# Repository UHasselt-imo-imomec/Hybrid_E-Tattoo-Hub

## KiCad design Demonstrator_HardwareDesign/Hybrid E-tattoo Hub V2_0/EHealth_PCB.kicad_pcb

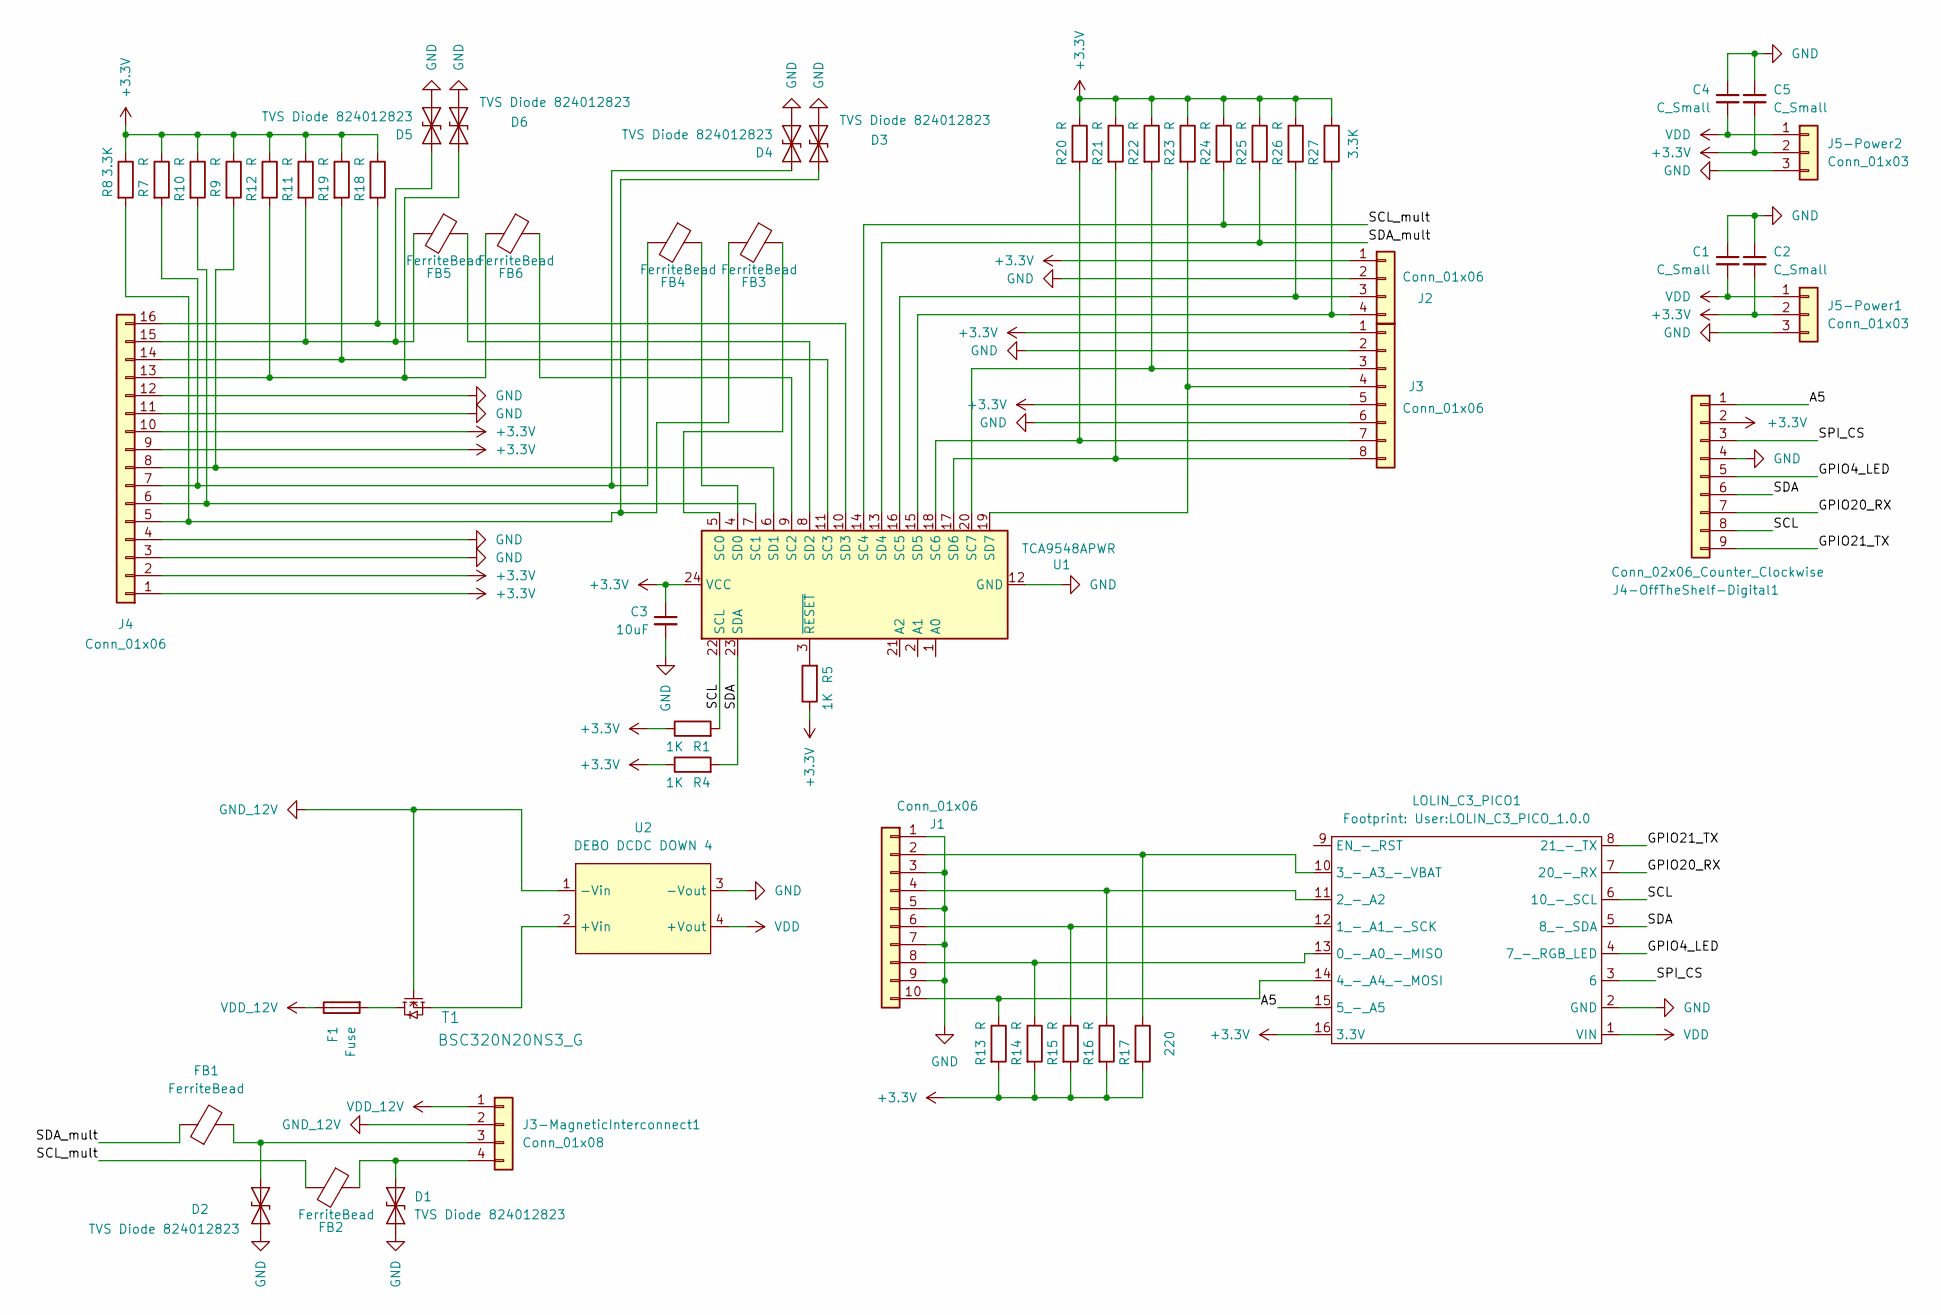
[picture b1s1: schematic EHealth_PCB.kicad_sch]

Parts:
C1, C2, C4, C5: C_Small; C_0805_2012Metric_Pad1.18x1.45mm_HandSolder
C3: 10uF; C_0805_2012Metric_Pad1.18x1.45mm_HandSolder
D1, D2, D3, D4, D5, D6: TVS Diode 824012823; R_0603_1608Metric_Pad0.98x0.95mm_HandSolder
F1: Fuse; Fuse_0805_2012Metric_Pad1.15x1.40mm_HandSolder
FB1, FB2, FB3, FB4, FB5, FB6: FerriteBead; R_0805_2012Metric_Pad1.20x1.40mm_HandSolder
J1: Conn_01x06; PinHeader_2x05_P2.54mm_Vertical
J2: Conn_01x06; PinHeader_1x04_P2.54mm_Vertical
J3: Conn_01x06; PinHeader_1x08_P2.54mm_Vertical
J3-MagneticInterconnect1: Conn_01x08; JST_VH_B4P-VH-B_1x04_P3.96mm_Vertical
J4: Conn_01x06; PinHeader_2x08_P2.54mm_Vertical
J4-OffTheShelf-Digital1: Conn_02x06_Counter_Clockwise; PinHeader_2x05_P2.54mm_Vertical
J5-Power1, J5-Power2: Conn_01x03; PinSocket_1x03_P2.54mm_Vertical
LOLIN_C3_PICO1: LOLIN_C3_PICO_1.0.0
R1, R4, R5: 1K; R_0805_2012Metric_Pad1.20x1.40mm_HandSolder
R7, R9, R10, R11, R12, R13, R14, R15, R16, R18, R19, R20, R21, R22, R23, R24, R25, R26: R; R_0805_2012Metric_Pad1.20x1.40mm_HandSolder
R8, R27: 3.3K; R_0805_2012Metric_Pad1.20x1.40mm_HandSolder
R17: 220; R_0805_2012Metric_Pad1.20x1.40mm_HandSolder
T1: BSC320N20NS3_G; Infineon_PG-TDSON-8_6.15x5.15mm; Voltage 200V
U1: TCA9548APWR; TSSOP-24_4.4x7.8mm_P0.65mm
U2: DEBO DCDC DOWN 4

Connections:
+3.3V: C2.2, C3.1, C5.2, J2.1, J3.1, J3.5, J4.1, J4.2, J4.9, J4.10, J4-OffTheShelf-Digital1.2, J5-Power1.2, J5-Power2.2, LOLIN_C3_PICO1.16 (3.3V), R1.1, R4.1, R5.1, R7.1, R8.1, R9.1, R10.1, R11.1, R12.1, R13.2, R14.2, R15.2, R16.2, R17.2, R18.1, R19.1, R20.1, R21.1, R22.1, R23.1, R24.1, R25.1, R26.1, R27.1, U1.24 (VCC); also elsewhere on the board
/A5: J4-OffTheShelf-Digital1.1, LOLIN_C3_PICO1.15 (5_-_A5)
/GPIO4_LED: J4-OffTheShelf-Digital1.5, LOLIN_C3_PICO1.4 (7_-_RGB_LED)
/GPIO20_RX: J4-OffTheShelf-Digital1.7, LOLIN_C3_PICO1.7 (20_-_RX)
/GPIO21_TX: J4-OffTheShelf-Digital1.9, LOLIN_C3_PICO1.8 (21_-_TX)
/SCL: J4-OffTheShelf-Digital1.8, LOLIN_C3_PICO1.6 (10_-_SCL), R1.2, U1.22 (SCL)
/SCL_mult: FB2.2, R24.2, U1.14 (SC4)
/SDA: J4-OffTheShelf-Digital1.6, LOLIN_C3_PICO1.5 (8_-_SDA), R4.2, U1.23 (SDA)
/SDA_mult: FB1.1, R25.2, U1.13 (SD4)
/SPI_CS: J4-OffTheShelf-Digital1.3, LOLIN_C3_PICO1.3 (6)
GND: C1.1, C2.1, C3.2, C4.1, C5.1, D1.1 (A1), D2.1 (A1), D3.1 (A1), D4.1 (A1), D5.1 (A1), D6.1 (A1), J1.1, J1.3, J1.5, J1.7, J1.9, J2.2, J3.2, J3.6, J4.3, J4.4, J4.11, J4.12, J4-OffTheShelf-Digital1.4, J5-Power1.3, J5-Power2.3, LOLIN_C3_PICO1.2 (GND), U1.12 (GND), U2.3 (-Vout); also elsewhere on the board
GND_12V: J3-MagneticInterconnect1.2, T1.4 (G), U2.1 (-Vin); also elsewhere on the board
unnamed 12: D1.2 (A2), FB2.1, J3-MagneticInterconnect1.4; also elsewhere on the board
unnamed 13: D2.2 (A2), FB1.2, J3-MagneticInterconnect1.3; also elsewhere on the board
unnamed: D3.2 (A2), FB3.2, J4.5, R8.2
unnamed: D4.2 (A2), FB4.2, J4.7, R7.2
unnamed: D5.2 (A2), FB5.2, J4.15, R11.2
unnamed: D6.2 (A2), FB6.2, J4.13, R12.2
unnamed: J1.2, LOLIN_C3_PICO1.10 (3_-_A3_-_VBAT), R17.1
unnamed: J1.4, LOLIN_C3_PICO1.11 (2_-_A2), R16.1
unnamed: J1.6, LOLIN_C3_PICO1.12 (1_-_A1_-_SCK), R15.1
unnamed: J1.8, LOLIN_C3_PICO1.13 (0_-_A0_-_MISO), R14.1
unnamed: J1.10, LOLIN_C3_PICO1.14 (4_-_A4_-_MOSI), R13.1
unnamed: J2.3, R26.2, U1.16 (SC5)
unnamed: J2.4, R27.2, U1.15 (SD5)
unnamed: J3.3, R22.2, U1.20 (SC7)
unnamed: J3.4, R23.2, U1.19 (SD7)
unnamed: J3.7, R20.2, U1.18 (SC6)
unnamed: J3.8, R21.2, U1.17 (SD6)
unnamed: J4.6, R10.2, U1.7 (SC1)
unnamed: J4.8, R9.2, U1.6 (SD1)
unnamed: J4.14, R19.2, U1.11 (SC3)
unnamed: J4.16, R18.2, U1.10 (SD3)
unnamed: F1.2, T1.5 (D)
unnamed: T1.1 (S), U2.2 (+Vin)
unnamed: FB3.1, U1.5 (SC0)
unnamed: FB6.1, U1.9 (SC2)
unnamed: FB4.1, U1.4 (SD0)
unnamed: FB5.1, U1.8 (SD2)
unnamed: R5.2, U1.3 (~RESET)
VDD: C1.2, C4.2, J5-Power1.1, J5-Power2.1, LOLIN_C3_PICO1.1 (VIN), U2.4 (+Vout); also elsewhere on the board
VDD_12V: F1.1, J3-MagneticInterconnect1.1; also elsewhere on the board

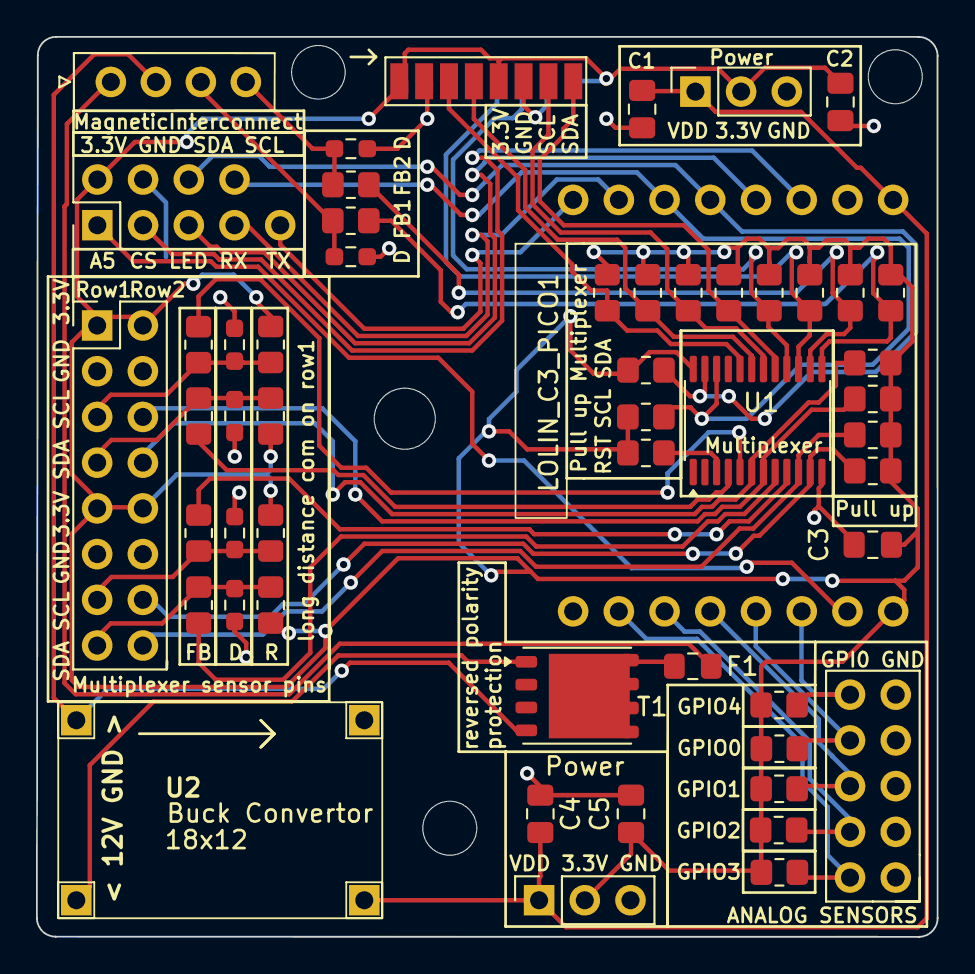
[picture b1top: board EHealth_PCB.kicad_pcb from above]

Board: 2 copper layers, 50.0 x 50.0 mm, 54 parts (1 on the bottom side), 42 nets.

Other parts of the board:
MagneticInterconnect: Conn_01x08; JST_VH_B4P-VH-B_1x04_P3.96mm_Vertical
Power: Conn_01x03; PinSocket_1x03_P2.54mm_Vertical
Power#2: Conn_01x03; PinSocket_1x03_P2.54mm_Vertical

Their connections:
+3.3V: Power.2, Power#2.2; also elsewhere on the board
GND: Power.3, Power#2.3; also elsewhere on the board
GND_12V: MagneticInterconnect.2; also elsewhere on the board
unnamed 12: MagneticInterconnect.4; also elsewhere on the board
unnamed 13: MagneticInterconnect.3; also elsewhere on the board
VDD: Power.1, Power#2.1; also elsewhere on the board
VDD_12V: MagneticInterconnect.1; also elsewhere on the board

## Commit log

2024-02-21 Adding datasheets and links pt1
2024-02-21 Adding datasheets and links pt2
2024-02-21 Initial commit, UNTESTED!
2024-02-21 Code compiles, added template secrets file.
2024-02-21 Added placeholder files.
2024-02-21 Added InfluxDB and Grafana pointers
2024-02-23 Test update from clone
2024-02-25 Laurence verandering
2024-02-25 Dit werkt?
2024-02-25 Deze code uitgetest met Arduino maar niet met esp
2024-02-26 ESP met multiplexer
2024-03-01 juiste Vout maar weerstand berekening klopt niet helemaal
2024-03-01 Code gebruikt om ppg data te bekijken
2024-03-01 Create ppg_Data
2024-03-01 PPG_Data
2024-03-01 Uitlezen van onbekende weerstand
2024-03-02 Minor modifications to the code, and some remarks!
2024-03-02 Started on demonstrator hardware design
2024-03-02 Added more elements to Demonstrator design
2024-03-03 Propere code van Thijs uit main gecombineerd met analoge sensor
2024-03-04 Data van ppg sensor met klipper rond vinger
2024-03-04 data collectie code
2024-03-04 alles erop en eraan
2024-03-04 Relocated Data folders
2024-03-04 Changed datatype (Line 164, to be tested)!
2024-03-05 Create Documentation
2024-03-06 test
2024-03-06 Update van Demonstrator
2024-03-06 json test file
2024-03-06 Added PCB design files
2024-03-10 uitlezen van alle sensoren, plotten in S studio
2024-03-10 code nog testen
2024-03-11 werkt: pin5, te doen: code voor 3 sensoren
2024-03-11 code uitlezen 3 temp sensoren, proper maken
2024-03-11 up_to_date_json_file
2024-03-13 alles werkende, code nog ordenen
2024-03-13 alles werkende
2024-03-13 alles
2024-03-13 Demonstrator met influxdb
2024-03-13 Demonstrator met SerialStudio
2024-03-14 blue led
2024-03-14 RGB led
2024-03-14 Full influxdb code ;et led
2024-03-14 secondje push led
2024-03-15 code up to date, pcb layout aanpassingen
2024-03-15 werkt maar code is niet clean
2024-03-16 Huidige optimale wifi&influx code
2024-03-16 aangepaste pcb layout
2024-03-16 foto van pcb
2024-03-16 foto pcb
2024-03-19 aangepaste layout
2024-03-20 layout met buck en mult chip
2024-03-22 schema met mult chip en buck convertor
2024-03-25 up to date
2024-03-28 huidige layout
2024-03-29 finished layout met logo
2024-03-29 Added fabrication files for hub v2 + small reorganisation.
2024-04-15 nieuwe pcb
2024-04-17 verbeterde layout
2024-04-18 Merge
2024-04-18 final product
2024-04-20 PCB up to date
2024-04-28 Added production files for V2.0
2024-05-03 zada
2024-07-20 New PCB
2024-10-08 Before sorting.
2024-10-08 Reshuffeled Hardware designfiles
2024-10-08 Moved other files
2024-10-08 Fix commit
